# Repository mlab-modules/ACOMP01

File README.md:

# ACOMP01 - Fast Analog Comparator Module

The ACOMP01 module is a high-speed dual comparator board with differential LVDS outputs. It is designed for fast signal discrimination in nanosecond-scale timing systems. Each comparator features coaxial MCX input connectors and differential output for integration into high-speed digital acquisition or timing logic circuits.

## Typical Applications

- High-speed pulse discrimination
- Oscilloscope triggering
- LIDAR and ToF sensing
- Nuclear and particle physics detectors
- Time interval measurement systems

## Features

- Two independent comparator channels
- High-speed response with sub-nanosecond propagation delay
- Differential LVDS outputs
- MCX connectors for analog input signals
- Designed for precise pulse timing and triggering

## Comparators Used

### TLV3604
- Propagation delay: 800 ps
- Toggle rate: up to 3 Gbps
- Input common-mode range: extends 200 mV beyond rails
- LVDS output with 350 mV typical differential swing
- Supply voltage: 2.4 V to 5.5 V
- Mounted as IC1【9†tlv3604.pdf】

### LMH7220
- Propagation delay: 2.9 ns
- Input voltage range extends 200 mV below ground
- LVDS output designed for 100 Ω differential load
- Supply voltage: 2.7 V to 12 V
- Mounted as IC2【8†lmh7220.pdf】

## Connectors

### Power Supply (J1)

- Onboard filtering capacitors: 10 µF, 1 µF, and 100 nF
- 5.6 V Zener diode for optional input voltage clamping and reverse voltage protection

The module uses (2.4 V to 5.5 V) for the two comparators. Ensure proper voltages are applied as per the comparator requirements.

### Inputs

- **J2, J3**: Inputs for TLV3604 (IN+, IN-)
- **J4, J5**: Inputs for LMH7220 (IN+, IN-)

All inputs are via MCX connectors with ground-referenced shielding.

### Outputs

- **J6**: LVDS differential output from TLV3604 (TLV_OUT+, TLV_OUT-)
- **J7**: LVDS differential output from LMH7220 (LMH_OUT+, LMH_OUT-)

> Each output is routed to a standard 3-pin header: OUT+, GND, OUT-

## Notes

DNF (Do Not Fit) resistors R1 and R2 are placeholders for optional output termination.

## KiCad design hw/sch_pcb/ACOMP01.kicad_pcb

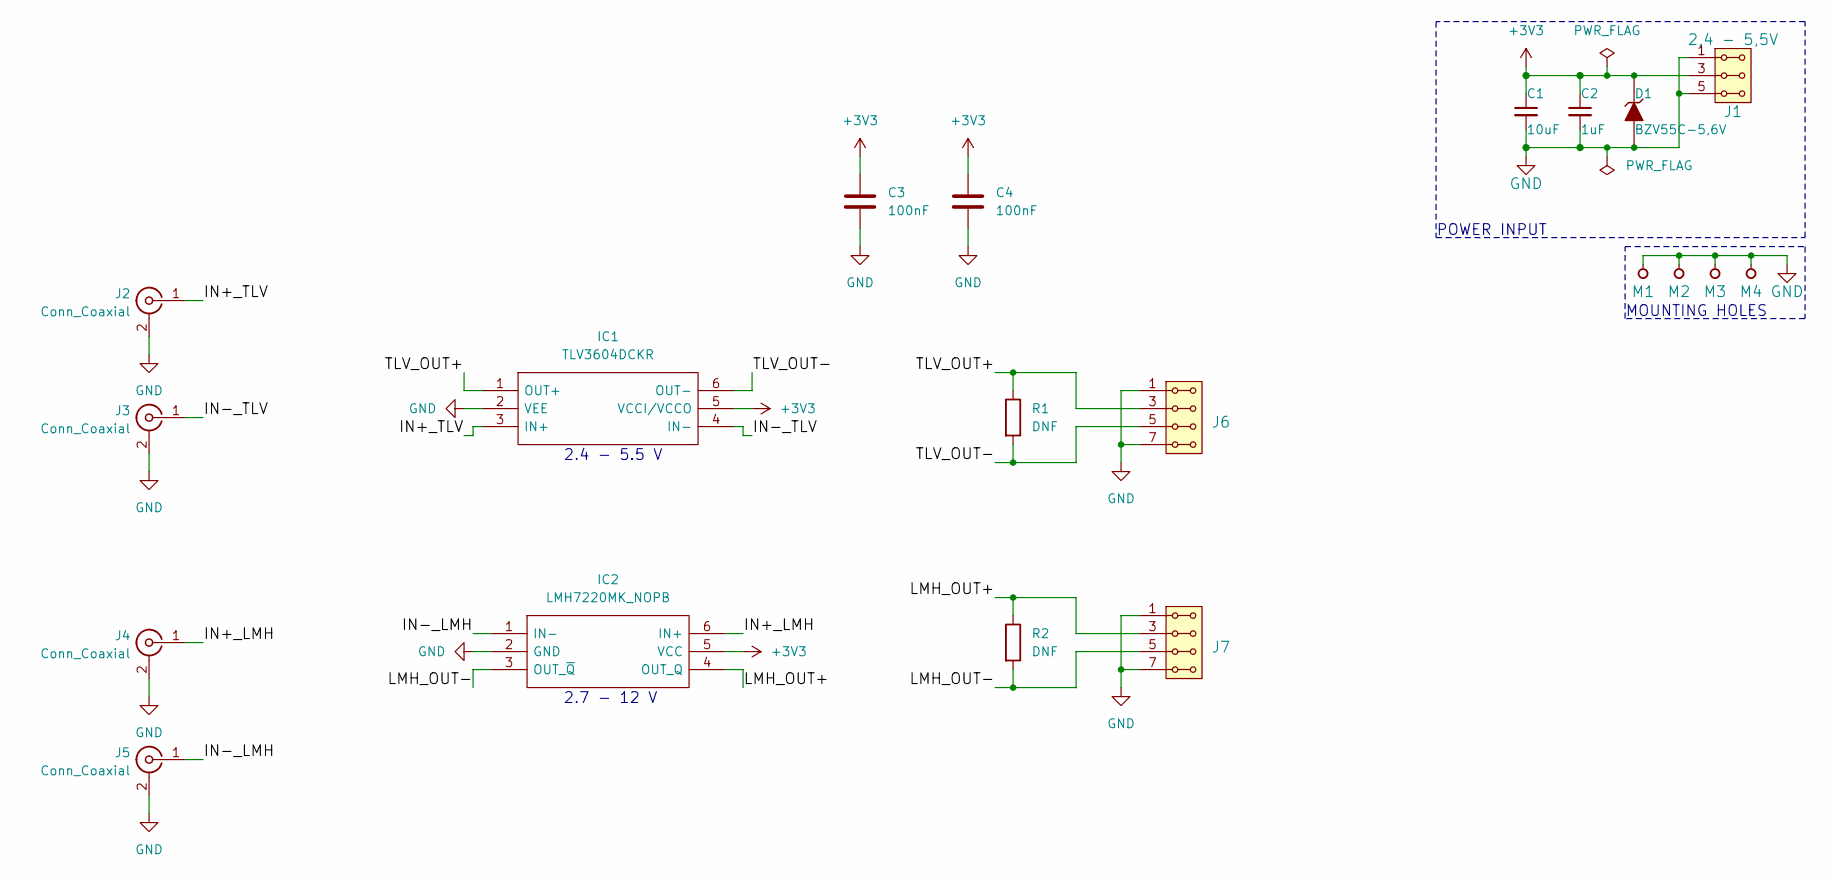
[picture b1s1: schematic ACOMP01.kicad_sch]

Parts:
C1: 10uF; C_0805_2012Metric
C2: 1uF; C_0805_2012Metric
C3, C4: 100nF; C_0805_2012Metric
D1: BZV55C-5,6V; D_SMA
IC1: TLV3604DCKR; SOT-363_SC-70-6; Mouser Part Number 595-TLV3604DCKR
IC2: LMH7220MK_NOPB; SOT-23-6; Mouser Part Number 926-LMH7220MK/NOPB
J1: 2,4 - 5,5V; Straight_2x03
J2, J3, J4, J5: Conn_Coaxial; SMA6251A13G50
J6, J7: HEADER_2x04_PARALLEL; Straight_2x04
M1, M2: HOLE M3; MountingHole_3mm
M3, M4: HOLE; MountingHole_3mm
R1, R2: DNF; R_0805_2012Metric

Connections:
+3V3: C1.1, C2.1, C3.1, C4.1, D1.1 (K), IC1.5 (VCCI/VCCO), IC2.5 (VCC), J1.3, J1.4
/IN+_LMH: IC2.6 (IN+), J4.1 (In)
/IN+_TLV: IC1.3 (IN+), J2.1 (In)
/IN-_LMH: IC2.1 (IN-), J5.1 (In)
/IN-_TLV: IC1.4 (IN-), J3.1 (In)
/LMH_OUT+: IC2.4 (OUT_Q), J7.3, J7.4, R2.1
/LMH_OUT-: IC2.3 (OUT_~Q), J7.5, J7.6, R2.2
/TLV_OUT+: IC1.1 (OUT+), J6.3, J6.4, R1.1
/TLV_OUT-: IC1.6 (OUT-), J6.5, J6.6, R1.2
GND: C1.2, C2.2, C3.2, C4.2, D1.2 (A), IC1.2 (VEE), IC2.2 (GND), J1.1, J1.2, J1.5, J1.6, J2.2 (Ext), J3.2 (Ext), J4.2 (Ext), J5.2 (Ext), J6.1, J6.2, J6.7, J6.8, J7.1, J7.2, J7.7, J7.8, M1.1, M2.1, M3.1, M4.1

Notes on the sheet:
POWER INPUT
2.4 - 5.5 V
MOUNTING HOLES
2.7 - 12 V

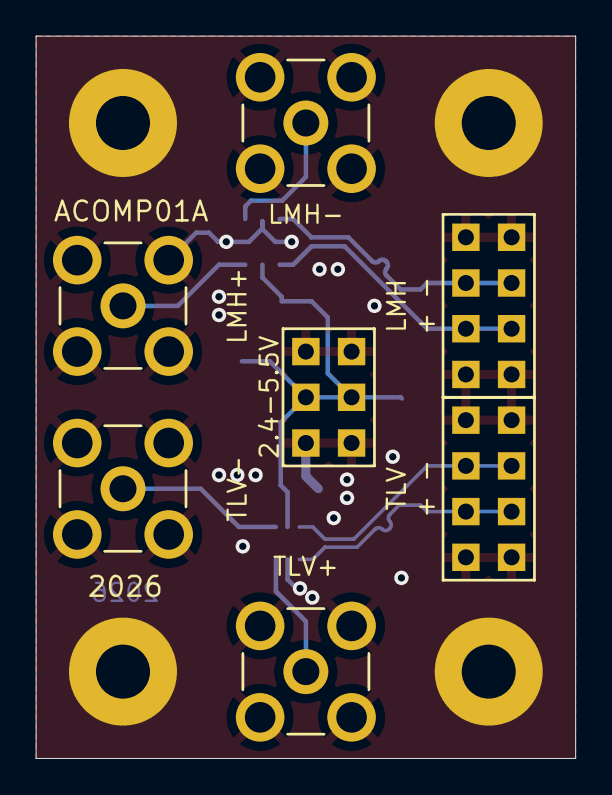
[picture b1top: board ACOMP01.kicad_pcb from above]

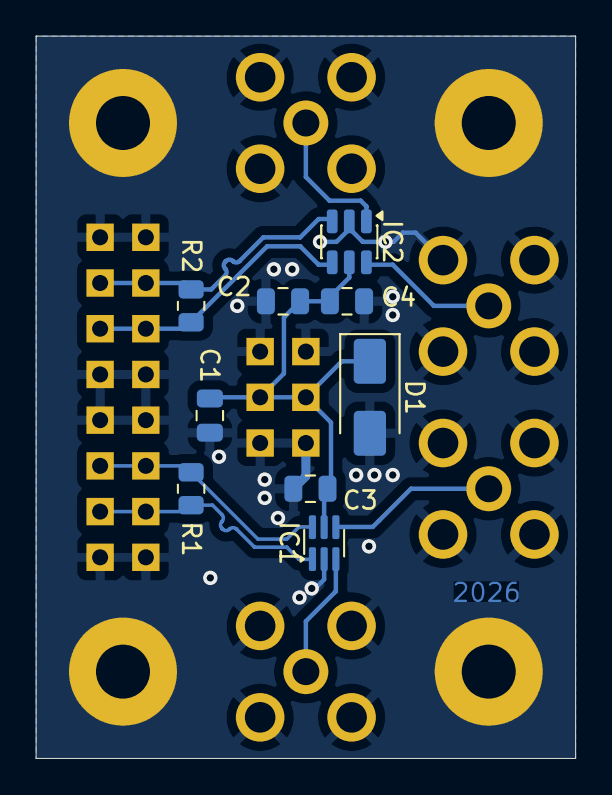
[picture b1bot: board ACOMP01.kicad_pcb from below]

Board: 2 copper layers, 30.0 x 40.1 mm, 20 parts (9 on the bottom side), 10 nets.

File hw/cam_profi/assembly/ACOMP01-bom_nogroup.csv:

Component,Description,Part,References,Value,Footprint,Quantity Per PCB,Datasheet,ust_id,height,mouser part number,mouser price/stock,manufacturer_name,manufacturer_part_number
1,Unpolarized capacitor,C,C3C4,100nF,C_0805_2012Metric,2,~,,,,,,
2,,C_Small-Device-ISM02A-rescue,C2,1uF,C_0805_2012Metric,1,,C0805_100n,,,,,
3,,C_Small-Device-ISM02A-rescue,C1,10uF,C_0805_2012Metric,1,,5c70984812875079b91f8bbe,,,,,
4,,D_ZENER-MLAB_D,D1,"BZV55C-5,6V",D_SMA,1,,5c70984512875079b91f88b2,,,,,
5,High Speed Comparator with LVDS Output,LMH7220MK_NOPB,IC2,LMH7220MK_NOPB,SOT-23-6,1,http://www.ti.com/lit/gpn/lmh7220,,1.1,926-LMH7220MK/NOPB,https://www.mouser.co.uk/ProductDetail/Texas-Instruments/LMH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,Texas Instruments,LMH7220MK/NOPB
6,800-ps high-speed rail-rail input comparator with LVDS outputs,TLV3604DCKR,IC1,TLV3604DCKR,SOT-363_SC-70-6,1,https://www.ti.com/lit/gpn/tlv3604,,1.1,595-TLV3604DCKR,https://www.mouser.co.uk/ProductDetail/Texas-Instruments/TLV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,Texas Instruments,TLV3604DCKR
7,"2x03 2.54 mm pitch header, 2 pins next to each other are connected",HEADER_2x03_PARALLEL,J1,"2,4 - 5,5V",Straight_2x03,1,,,,,,,
8,"coaxial connector (BNC, SMA, SMB, SMC, Cinch/RCA, LEMO, ...)",Conn_Coaxial,J2J3J4J5,Conn_Coaxial,SMA6251A13G50,4, ~,,,,,,
9,"2x04 2.54 mm pitch header, 2 pins next to each other are connected",HEADER_2x04_PARALLEL,J6J7,HEADER_2x04_PARALLEL,Straight_2x04,2,,,,,,,

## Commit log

2023-02-09 tetst commit
2023-02-09 submodules initialization
2023-02-09 .github added
2023-02-09 new readme
2023-02-09 schematics added
2023-02-09 Update actions products
2023-02-09 update assets
2023-02-10 Update workflow files
2023-02-11 Cleanup and remove unused kicad worksheet template.
2023-02-12 Update metadata files
2023-04-12 pcb layout
2023-04-13 pcb layout finished, ready for check
2023-05-28 automated commit; add github actions
2023-06-09 Cleanup of some DRC errors.
2023-07-05 automated commit; rename source files to new naming convence
2023-09-16 Update status
2026-01-18 Update project to KiCADv9. Resolved #1
2026-01-18 Improve documentation.
